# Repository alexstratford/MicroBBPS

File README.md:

# MicroBBPS
<h3>Breadboard Power Supply</h3>
<BR CLEAR=”left” />

A small, USB-C connected power supply designed to fit onto the power rails of a solderless breadboard.

For each side, you can select between 3.3 & 5.0 Volt linear regulators, or the input voltage at the screw terminal. 

The integrated version adds 26 breadboard rows and 2 continuous power rails. So you can turn those prototypes into something more permanent with an easy microUSB power connector.

<h4><a href="https://github.com/stasiselectronics/MicroBBPS/tree/variant-integrated">Check out the integrated version's repository branch</a></h4>

## Documentation

If you would like to read more about how the design works and see some of the technical information, be sure to check out the documentation site that accompanies this project.

<h3><a href="https://stasiselectronics.github.io/MicroBBPS/">Read the Docs</a></h3>

This site is hosted on Github Pages, a great way to deploy your own static website using jekyll. It uses the wonderful theme [Minimal Mistakes](https://mmistakes.github.io/minimal-mistakes/about/) by Michael Rose.

[Learn more about github pages.](https://pages.github.com/)

## Development
This open source hardware project is developed using KiCAD and inkscape. It exists as a schematic and pcb design, with supporting files to create the necesarry output files for Printed Circuit Board fabrication.

[Learn more about KiCAD](https://kicad.org/about/kicad/)

## Updates
If you would like to keep up to date with this project, be sure to check out the original creator's instagram

<h3><a href="https://www.instagram.com/stasis.electronics/">stasis.electronics</a></h3>

### A02 Fabrication

After incorporating the design changes from the first revision, the second revision came out great! 

There are still a few details to try and adjust for any future fabrication.
- Silkscreen adjustments for better image fidelity
- Still have some mechanical rocking on the solderless version when inserted into a breadboard

Some of the major changes between on A02 from A01 are
- Smaller board shape
- Changed LEDs to 1206 for better part availability and easier hand soldering
- Larger silkscreen features
- Integrated version

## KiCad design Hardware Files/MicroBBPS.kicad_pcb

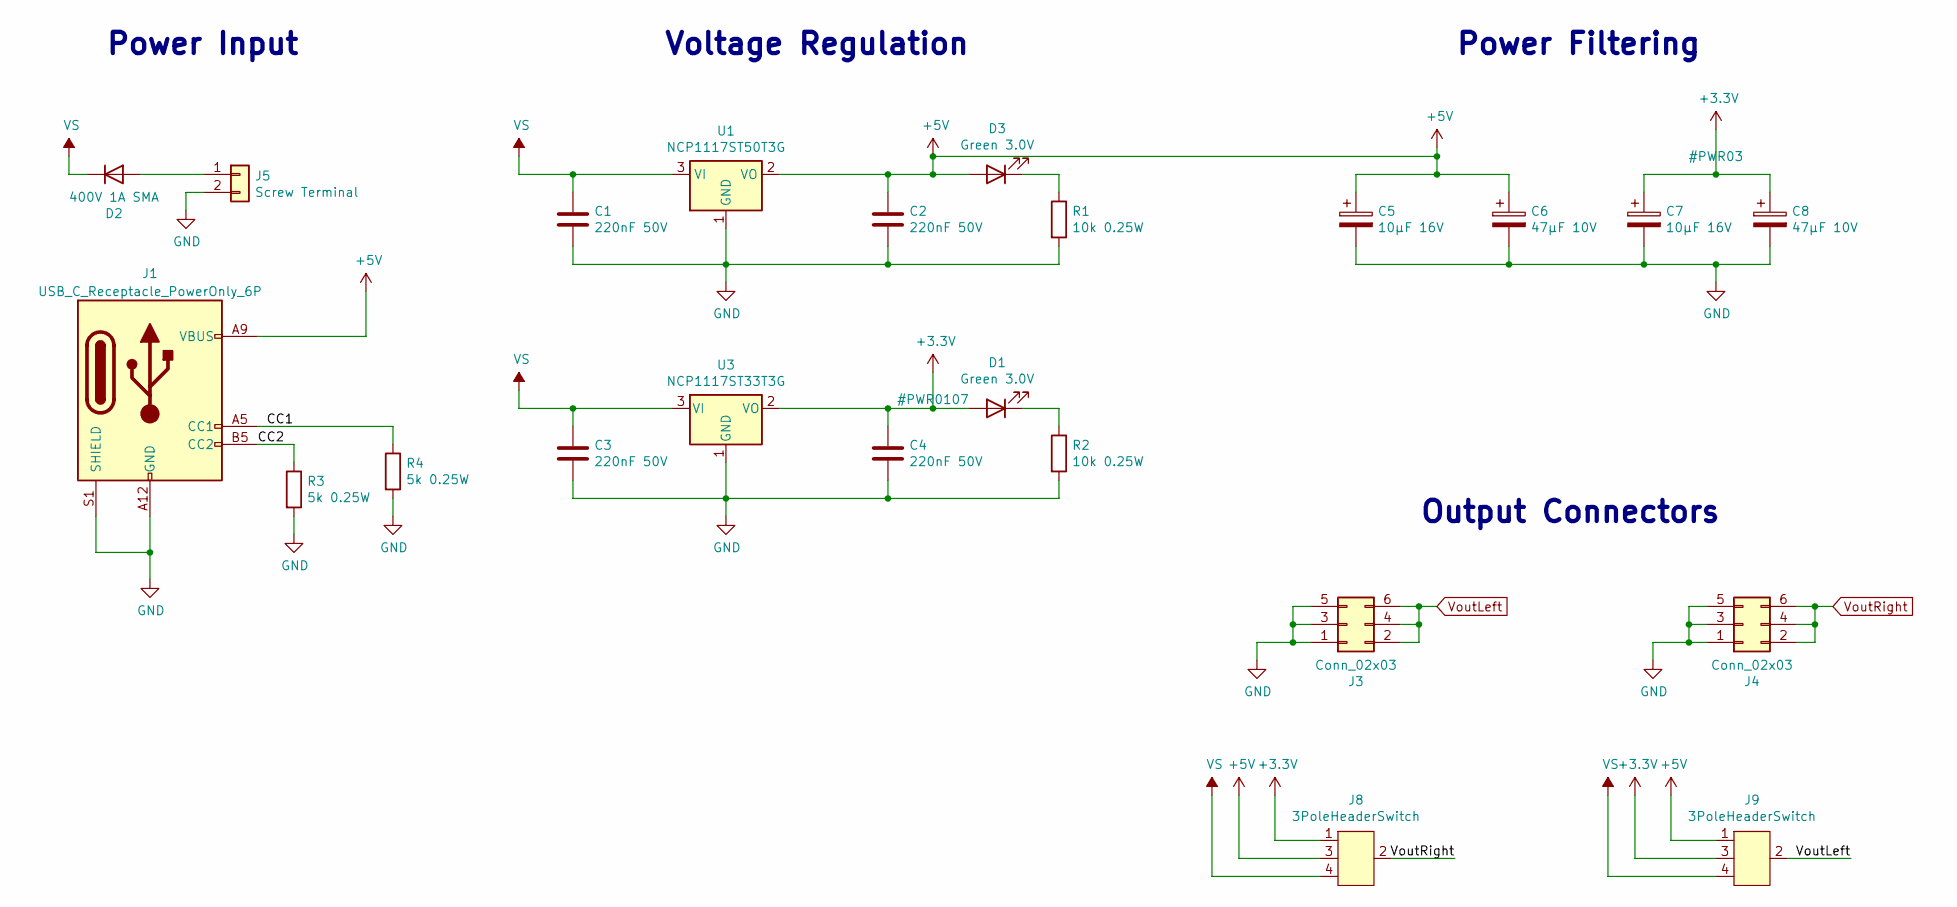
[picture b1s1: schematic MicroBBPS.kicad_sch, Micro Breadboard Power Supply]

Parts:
C1, C2, C3, C4: 220nF 50V; C_1206_3216Metric_Pad1.33x1.80mm_HandSolder
C5, C7: 10µF 16V; CP_Elec_4x5.4
C6, C8: 47µF 10V; CP_Elec_4x5.4
D1, D3: Green 3.0V; D_1206_3216Metric_Pad1.42x1.75mm_HandSolder
D2: 400V 1A SMA; D_SMA
J1: USB_C_Receptacle_PowerOnly_6P; GT-USB-7002C
J3, J4: Conn_02x03; PinHeader_2x03_P2.54mm_Vertical
J5: Screw Terminal; WJ124-3.81-2P
J8, J9: 3PoleHeaderSwitch
R1, R2: 10k 0.25W; R_1206_3216Metric_Pad1.30x1.75mm_HandSolder
R3, R4: 5k 0.25W; R_1206_3216Metric_Pad1.30x1.75mm_HandSolder
U1: NCP1117ST50T3G; SOT-223-3_TabPin2
U3: NCP1117ST33T3G; SOT-223-3_TabPin2

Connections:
+3.3V: C4.1, C7.1, C8.1, D1.2 (A), J8.1, J9.3, U3.2 (VO)
+5V: C2.1, C5.1, C6.1, D3.2 (A), J1.A9 (VBUS), J1.B9 (VBUS), J8.3, J9.1, U1.2 (VO)
/CC1: J1.A5 (CC1), R4.1
/CC2: J1.B5 (CC2), R3.1
GND: C1.2, C2.2, C3.2, C4.2, C5.2, C6.2, C7.2, C8.2, J1.A12 (GND), J1.B12 (GND), J1.S1 (SHIELD), J3.1, J3.3, J3.5, J4.1, J4.3, J4.5, J5.2, R1.2, R2.2, R3.2, R4.2, U1.1 (GND), U3.1 (GND)
unnamed: D1.1 (K), R2.1
unnamed: D2.2 (A), J5.1
unnamed: D3.1 (K), R1.1
VS: C1.1, C3.1, D2.1 (K), J8.4, J9.4, U1.3 (VI), U3.3 (VI)
VoutLeft: J3.2, J3.4, J3.6, J9.2
VoutRight: J4.2, J4.4, J4.6, J8.2

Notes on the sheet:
Output Connectors
Power Input
Voltage Regulation
Power Filtering

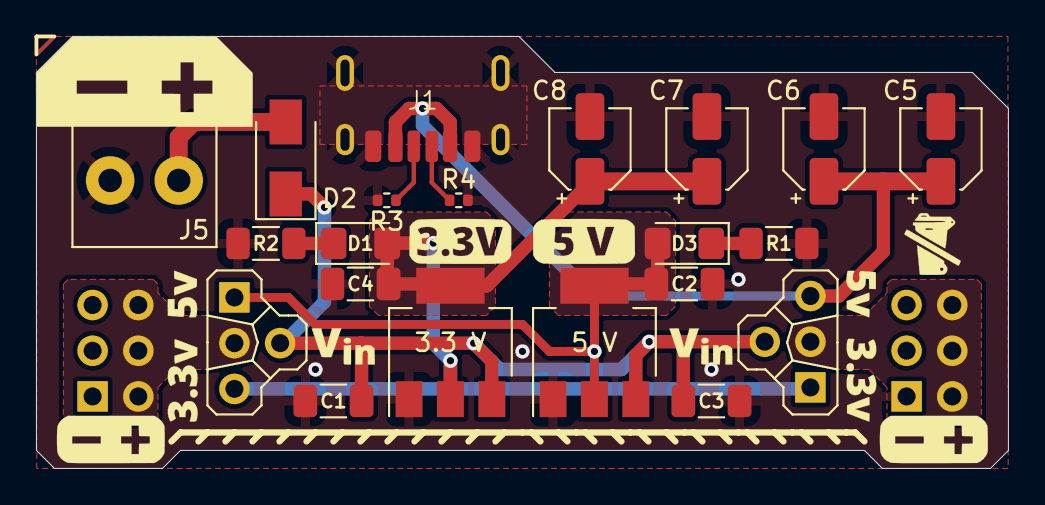
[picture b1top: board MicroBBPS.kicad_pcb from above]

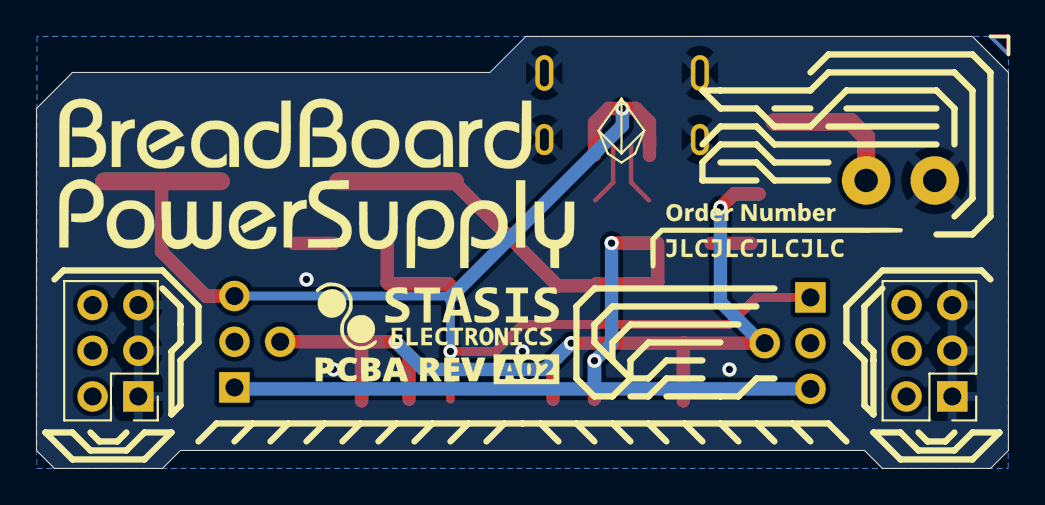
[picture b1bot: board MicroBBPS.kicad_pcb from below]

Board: 2 copper layers, 54.0 x 24.0 mm, 23 parts (2 on the bottom side), 11 nets.

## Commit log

2023-03-29 Adding USB-C Files
2023-04-13 Updating to USB-C

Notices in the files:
Hardware Files/MicroBBPS.kicad_sch:
License: CERN-OHL-S
